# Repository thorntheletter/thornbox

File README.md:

# thornbox
Custom stickless controller compatible (probably) with most Brooks boards

This is my first time doing PCB design, CAD, and 3D printing so it is probably a bit rough.

## Current Issues:
* The DIP Switch description for tournament lockout is reversed.
* There is not enough room in the top of the case for player LEDs.
* Snackbox Micro buttons end up awkwardly high.
* 3D Printed buttons can be fragile and break easily.
* DP/LS/RS switches do not work. (I believe this to be a problem on the PCB manufacturers end.)
* The screws needing to go from bottom to top through PCB are tricky to get in right.
* I did not have the filament to iterate the tolerances more than once after fixing underextrusion.
* The files to generate pcb graphics footprints are missing (I may also need the hotswap socket / USB-C port footprints)
* The USB-C port is a pain to solder by hand.

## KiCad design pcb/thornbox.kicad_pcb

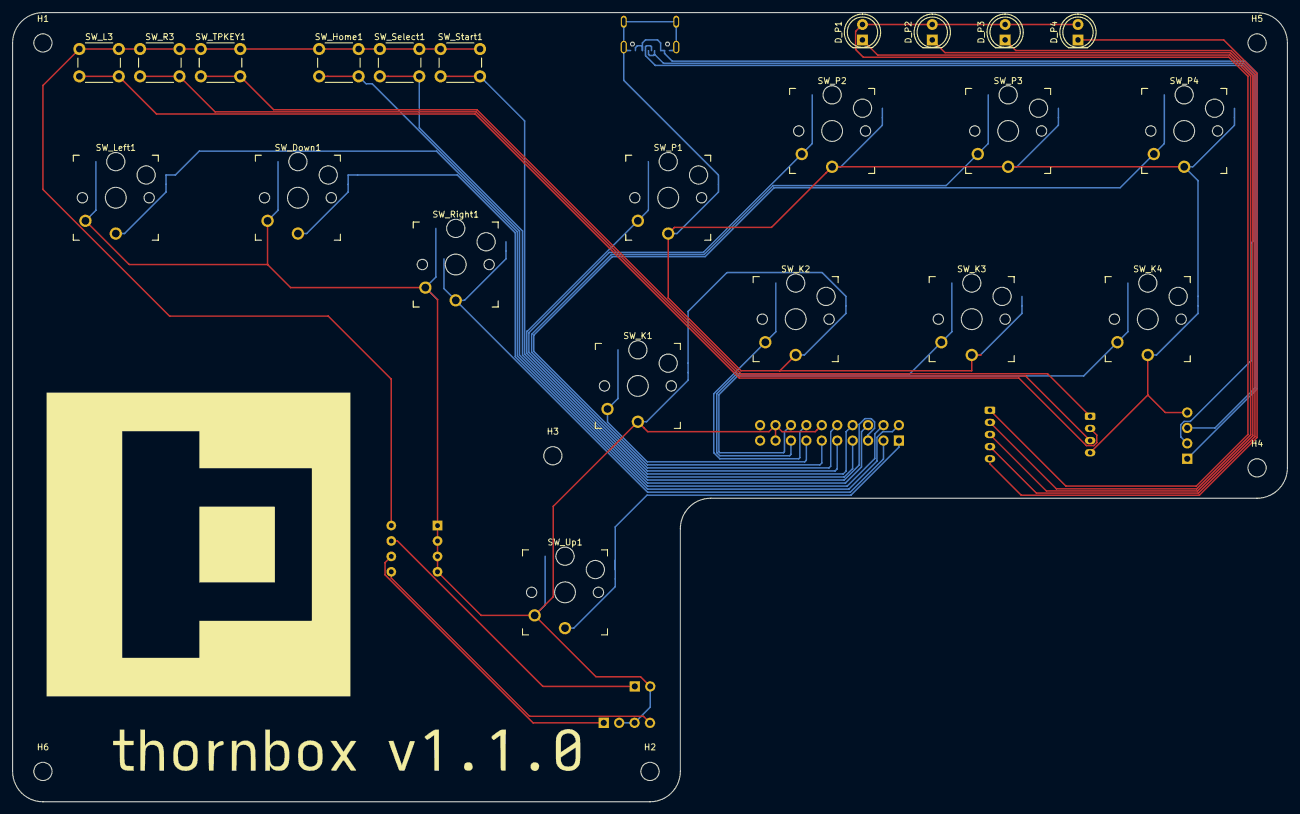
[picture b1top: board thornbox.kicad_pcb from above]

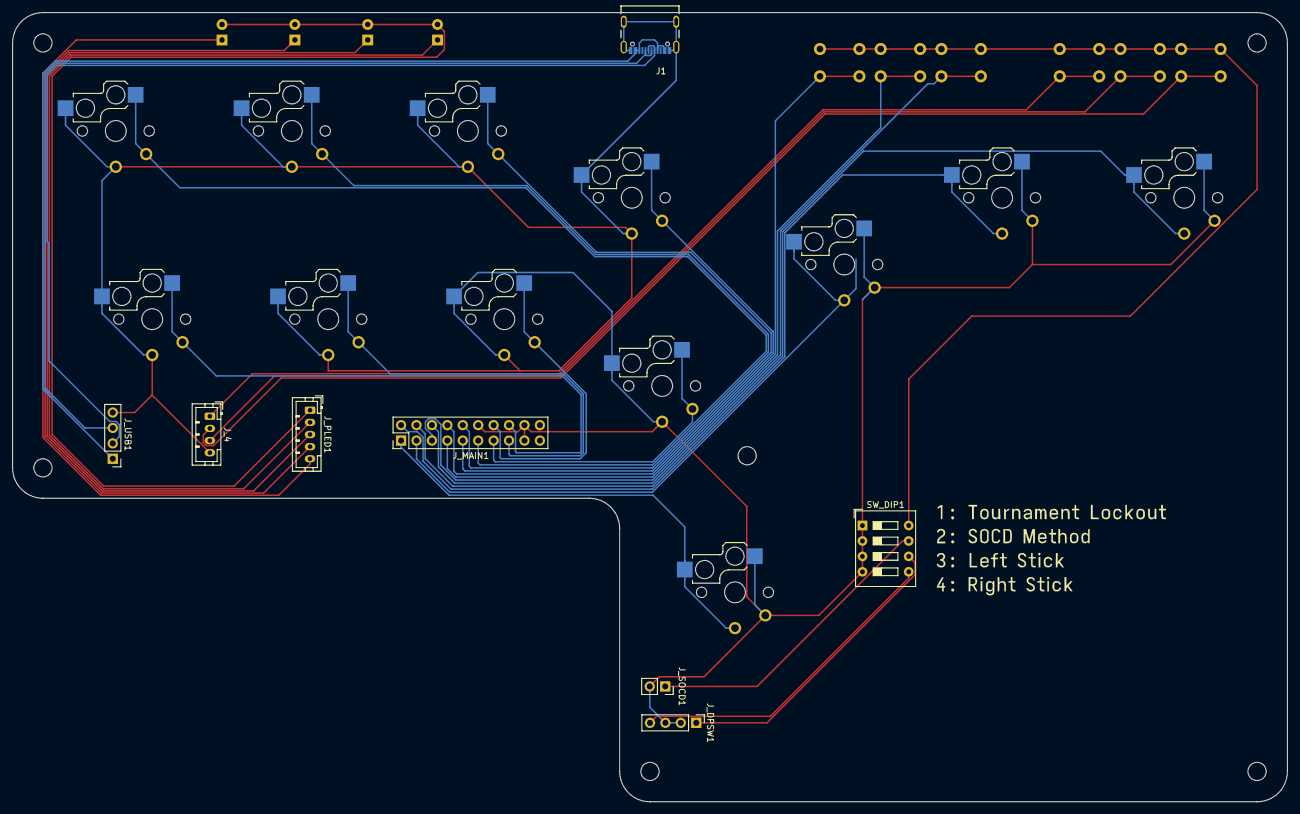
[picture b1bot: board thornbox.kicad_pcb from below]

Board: 2 copper layers, 210.0 x 130.0 mm, 39 parts (9 on the bottom side), 31 nets.

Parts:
DIPtext1: MountingHole; diplabel
D_P1, D_P2, D_P3, D_P4: LED; LED_D5.0mm
H1, H2, H3, H4, H5, H6: MountingHole; MountingHole_3mm
J1: USB4105-GF-A; GCT_USB4105-GF-A
J_4: Conn_01x04_Male; JST_PH_B4B-PH-K_1x04_P2.00mm_Vertical
J_DPSW1: Conn_01x04; PinHeader_1x04_P2.54mm_Vertical
J_MAIN1: Conn_02x20_Odd_Even; PinHeader_2x10_P2.54mm_Vertical
J_PLED1: Conn_01x05; JST_PH_B5B-PH-K_1x05_P2.00mm_Vertical
J_SOCD1: Conn_01x02; PinSocket_1x02_P2.54mm_Vertical
J_USB1: Conn_01x04_Male; PinHeader_1x04_P2.54mm_Vertical
Logo1: MountingHole; thethorn5
SW_DIP1: SW_DIP_x04; SW_DIP_SPSTx04_Slide_9.78x12.34mm_W7.62mm_P2.54mm
SW_Down1: SW_Push; Kailh_socket_PG1350_optional
SW_Home1: SW_Push; SW_PUSH_6mm
SW_K1, SW_K2, SW_K3, SW_K4: SW_Push; Kailh_socket_PG1350_optional
SW_L3: SW_Push; SW_PUSH_6mm
SW_Left1: SW_Push; Kailh_socket_PG1350_optional
SW_P1, SW_P2, SW_P3, SW_P4: SW_Push; Kailh_socket_PG1350_optional
SW_R3: SW_Push; SW_PUSH_6mm
SW_Right1: SW_Push; Kailh_socket_PG1350_optional
SW_Select1: SW_Push; SW_PUSH_6mm
SW_Start1: SW_Push; SW_PUSH_6mm
SW_TPKEY1: SW_Push; SW_PUSH_6mm
SW_Up1: SW_Push; Kailh_socket_PG1350_optional
version1: MountingHole; version

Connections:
Earth: J1.A1_B12, J1.B1_A12, J1.S1, J1.S2, J1.S3, J1.S4, J_4.4, J_DPSW1.2, J_DPSW1.3, J_MAIN1.12, J_MAIN1.17, J_MAIN1.18, J_SOCD1.2, J_USB1.4, SW_DIP1.1, SW_DIP1.2, SW_DIP1.3, SW_DIP1.4, SW_Down1.1, SW_K1.2, SW_K2.2, SW_K3.2, SW_K4.2, SW_Left1.1, SW_P1.2, SW_P2.2, SW_P3.2, SW_P4.2, SW_Right1.1, SW_Up1.1
unnamed: D_P1.1, J_PLED1.2
unnamed: D_P1.2, D_P2.2, D_P3.2, D_P4.2, J_PLED1.1
unnamed: D_P2.1, J_PLED1.3
unnamed: D_P3.1, J_PLED1.4
unnamed: D_P4.1, J_PLED1.5
unnamed: J1.A4_B9, J1.A5, J1.B4_A9, J1.B5, J_USB1.1
unnamed: J1.A6, J1.B6, J_USB1.3
unnamed: J1.A7, J1.B7, J_USB1.2
unnamed: J_4.1, SW_TPKEY1.2
unnamed: J_4.2, SW_L3.2
unnamed: J_4.3, SW_R3.2
unnamed: J_DPSW1.1, SW_DIP1.6
unnamed: J_DPSW1.4, SW_DIP1.5
unnamed: J_MAIN1.1, SW_Up1.2
unnamed: J_MAIN1.2, SW_Down1.2
unnamed: J_MAIN1.3, SW_Right1.2
unnamed: J_MAIN1.4, SW_Left1.2
unnamed: J_MAIN1.5, SW_Select1.2
unnamed: J_MAIN1.6, SW_Home1.2
unnamed: J_MAIN1.7, SW_Start1.2
unnamed: J_MAIN1.8, SW_P1.1
unnamed: J_MAIN1.9, SW_P2.1
unnamed: J_MAIN1.10, SW_P3.1
unnamed: J_MAIN1.11, SW_P4.1
unnamed: J_MAIN1.13, SW_K1.1
unnamed: J_MAIN1.14, SW_K2.1
unnamed: J_MAIN1.15, SW_K3.1
unnamed: J_MAIN1.16, SW_K4.1
unnamed: J_SOCD1.1, SW_DIP1.7
unnamed: SW_DIP1.8, SW_Home1.1, SW_L3.1, SW_R3.1, SW_Select1.1, SW_Start1.1, SW_TPKEY1.1

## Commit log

2021-10-01 initial commit: thornbox 1.1.0 (missing some files)
2021-10-01 added gerbers
2021-10-01 Create LICENSE
2021-10-01 added more current issues in readme and gitignore
